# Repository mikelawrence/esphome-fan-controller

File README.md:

# ESPHome RGBCCT LED Controller

<p align="center">

</p>

This is a simple ESP32-C3 based fan controller design to support 4-pin computer fans from 5V to 24V at up to 2 amps. Fan tachometer is supported.

## Web Installation

Goto [Github Pages](https://mikelawrence.github.io/esphome-fan-controller/) if you want to install a prebuilt image and receive automatic update notifications via Home Assistant.

## Status

* **Rev -:** Ordered boards from JLCPCB. Ordered parts from Mouser and Digikey. Board is assembled but there is a problem with the 5V Power Supply. Wait for Rev A.
* **Rev A:** Coming soon!

## Schematic

<p align="center">
     <br />
    Schematic
</p>

## Bill of Materials

<p align="center">
     <br />
    Interactive BOM
</p>

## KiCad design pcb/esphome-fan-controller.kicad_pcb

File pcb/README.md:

# ESPHome RGBCCT LED Controller PCB

<p align="center">

</p>

This is a simple ESP32-C3 based fan controller design to support 4-pin computer fans from 5V to 24V at up to 2 amps. Fan tachometer is supported.

## Status

* **Rev -:** Ordered boards from JLCPCB. Ordered parts from Mouser and Digikey. Currently waiting to put everything together.

## Schematic

<p align="center">
     <br />
    Schematic
</p>

## Bill of Materials

<p align="center">
     <br />
    Interactive BOM
</p>

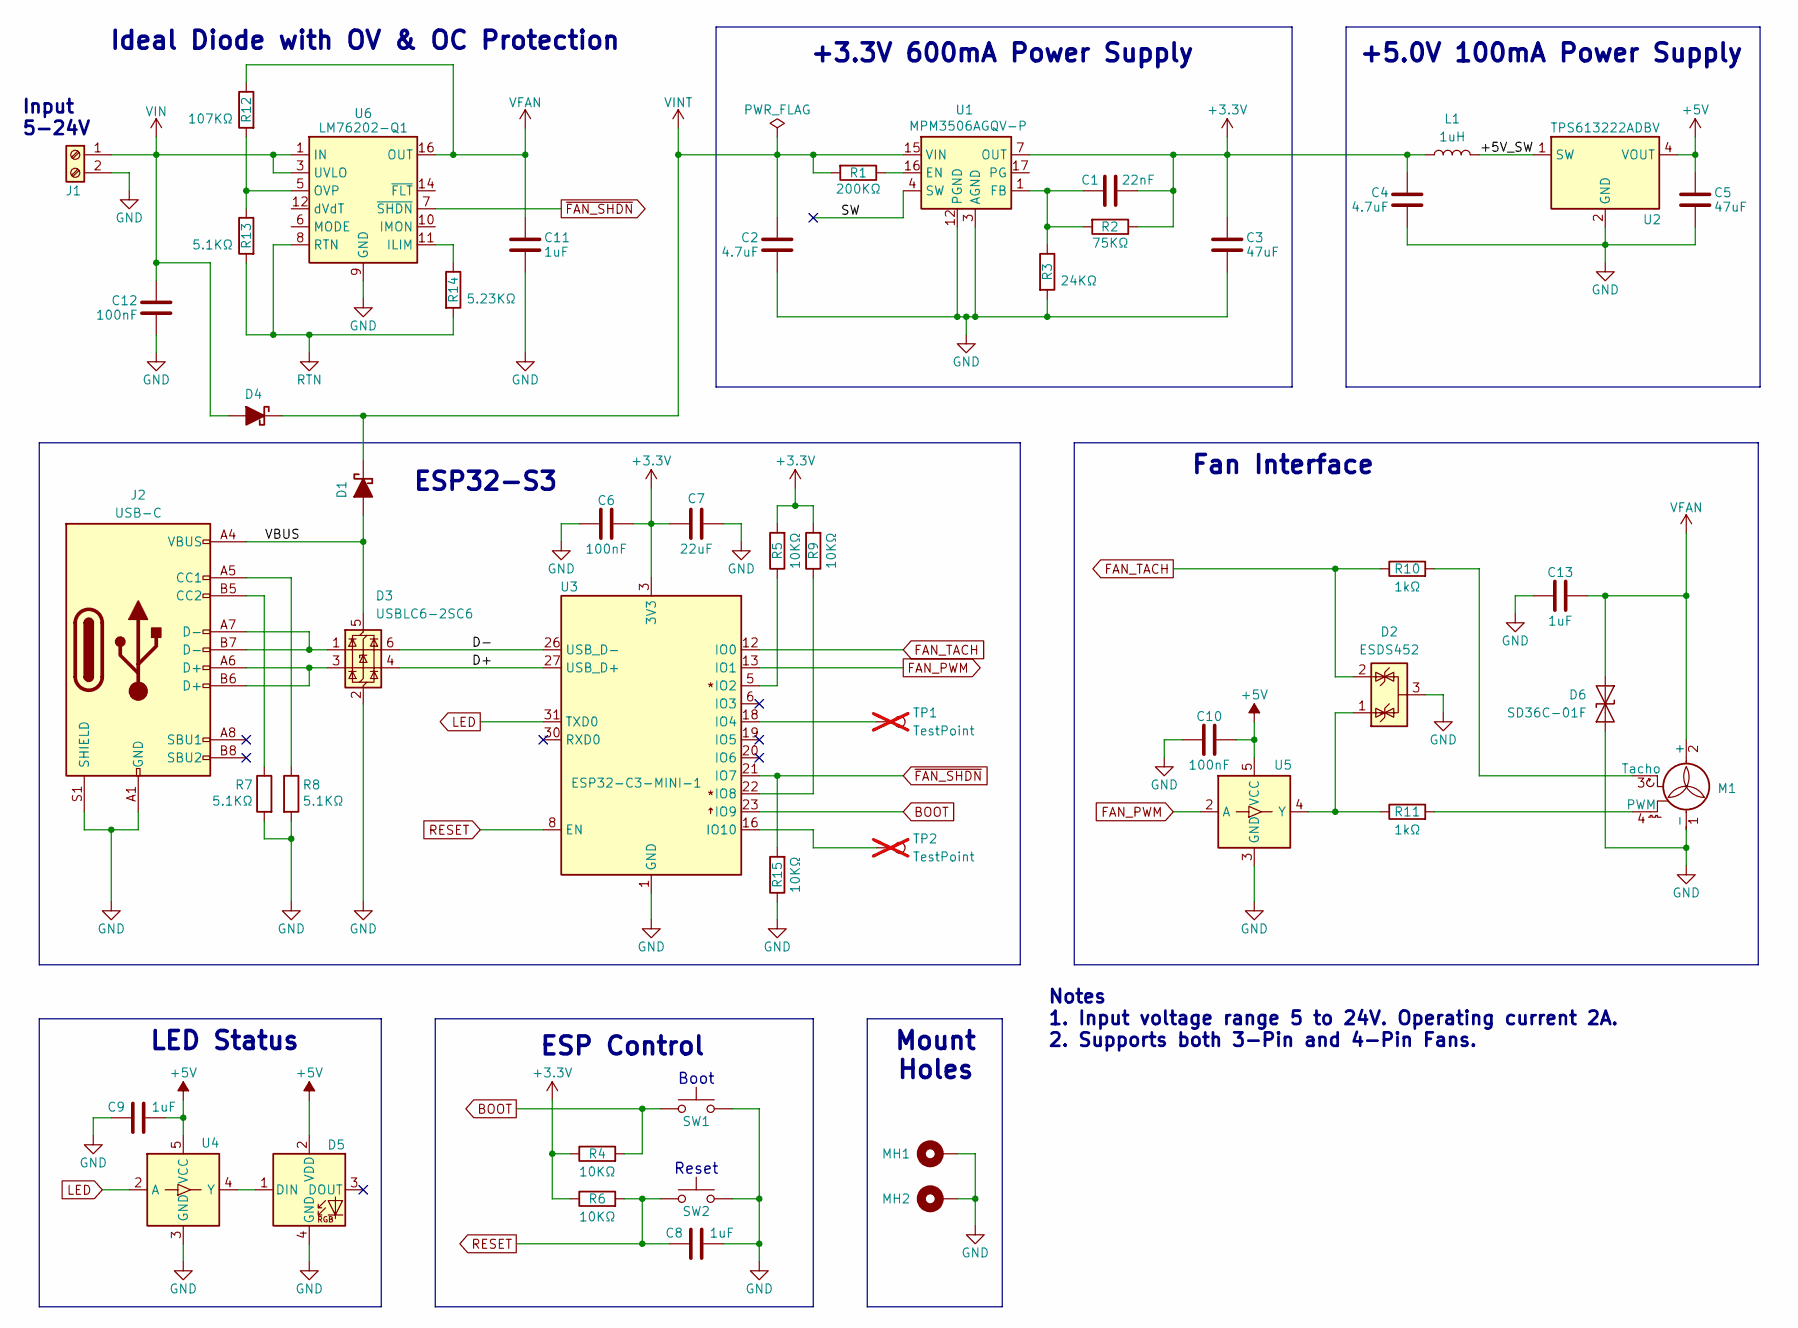
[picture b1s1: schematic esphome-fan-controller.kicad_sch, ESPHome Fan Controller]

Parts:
C1: 22nF; C_0402_1005Metric; Part Number GRM155R71H223KA12J
C2, C4: 4.7uF; C_0805_2012Metric; Part Number MSASU21GBB5475KTNA01
C3, C5: 47uF; C_0805_2012Metric; Part Number MSASL21GBB5476MTNA01
C6, C10, C12: 100nF; C_0402_1005Metric; Part Number CL05B104KB54PNC
C7: 22uF; C_0603_1608Metric; Part Number GRM188R60J226MEA0D
C8, C9: 1uF; C_0402_1005Metric; Part Number CL05A105KA5NQNC
C11, C13: 1uF; C_0805_2012Metric; Part Number CC0805MKY5V9BB105
D1, D4: SS2FH6HM3/H; D_SMF; Part Number SS2FH6HM3/H
D2: ESDS452; SOT-23; Part Number ESDS452DBZR
D3: USBLC6-2SC6; SOT-23-6; Part Number USBLC6-2SC6
D5: SK6812-4020; Part Number 4691
D6: SD36C-01F; D_SOD-323; Part Number SD36C-01FTG
J1: Screw_Terminal_01x02; 1984769; Part Number 1988956
J2: USB-C; HRO_TYPE-C-31-M-12; Part Number 1332645
L1: 1uH; L_0805_2012Metric; Part Number MLP2012S1R0MT0S1
M1: Fan_CPU_4pin; FanPinHeader_1x04_P2.54mm_Vertical; Part Number 47053-1000
MH1, MH2: MountingHole_2.2mm_M2_Pad
R1: 200KΩ; R_0402_1005Metric; Part Number CRCW0402200KFKED
R2: 75KΩ; R_0402_1005Metric; Part Number RT0402BRD0775KL
R3: 24KΩ; R_0402_1005Metric; Part Number RT0402BRD0724KL
R4, R5, R6, R9, R15: 10KΩ; R_0402_1005Metric; Part Number CRCW040210K0FKED
R7, R8, R13: 5.1KΩ; R_0402_1005Metric; Part Number RT0402BRD075K1L
R10, R11: 1kΩ; R_0402_1005Metric; Part Number CRCW04021K0FKED
R12: 107KΩ; R_0402_1005Metric; Part Number RT0402BRD07107KL
R14: 5.23KΩ; R_0402_1005Metric; Part Number RT0402BRD075K23L
SW1, SW2: SW_SPST_B3U-1000P-B; Part Number B3U-1000P
TP1, TP2: TestPoint; TestPoint_THTPad_1.0x1.0mm_Drill0.5mm; not fitted
U1: MPM3506AGQV-P; QFN-19; Part Number MPM3506AGQV-P; Mouser Part Number 946-MPM3506AGQV-P
U2: TPS613222ADBV; SOT-23-5; Part Number TPS613222ADBVR
U3: ESP32-C3-MINI-1; ESP32-C3-MINI-1-N4X; Part Number ESP32-C3-MINI-1-N4X
U4, U5: SN74LV1T34DBV; SOT-23-5; Part Number SN74LV1T34DBV
U6: LM76202-Q1; HTSSOP-16-1EP_4.4x5mm_P0.65mm_EP3.4x5mm_Mask2.66x2.46mm_The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; Part Number LM76202QPWPRQ1

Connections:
+3.3V: C1.2, C3.1, C4.1, C6.2, C7.1, L1.1, R2.1, R4.1, R5.2, R6.1, R9.2, U1.7 (OUT), U1.8 (OUT_2), U1.9 (OUT_3), U1.19 (OUT_4), U3.3 (3V3)
+5V: C5.1, C9.2, C10.2, D5.2 (VDD), U2.4 (VOUT), U4.5 (VCC), U5.5 (VCC)
/+5V_SW: L1.2, U2.1 (SW)
/D+: D3.4 (I/O2), U3.27 (USB_D+)
/D-: D3.6 (I/O1), U3.26 (USB_D-)
/SW: U1.4 (SW), U1.5 (SW_2), U1.6 (SW_3), U1.18 (SW_4)
/VBUS: D1.2 (A), D3.5 (VBUS), J2.A4 (VBUS), J2.B4 (VBUS)
BOOT: R4.2, SW1.2, U3.23 (IO9)
FAN_PWM: U3.13 (IO1), U5.2 (A)
FAN_TACH: D2.2 (K), R10.1, U3.12 (IO0)
GND: C2.2, C3.2, C4.2, C5.2, C6.1, C7.2, C8.2, C9.1, C10.1, C11.2, C12.2, C13.1, D2.3 (A), D3.2 (GND), D5.4 (GND), D6.1 (A1), J1.2, J2.A1 (GND), J2.B1 (GND), J2.S1 (SHIELD), M1.1 (-), MH1.1, MH2.1, R3.2, R7.2, R8.2, R15.1, SW1.1, SW2.1, U1.3 (AGND), U1.12 (PGND), U1.13 (PGND_2), U2.2 (GND), U3.1 (GND), U3.2 (GND), U3.11 (GND), U3.14 (GND), U3.36 (GND), U3.37 (GND), U3.38 (GND), U3.39 (GND), U3.40 (GND), U3.41 (GND), U3.42 (GND), U3.43 (GND), U3.44 (GND), U3.45 (GND), U3.46 (GND), U3.47 (GND), U3.48 (GND), U3.49 (GND), U3.50 (GND), U3.51 (GND), U3.52 (GND), U3.53 (GND), U4.3 (GND), U5.3 (GND), U6.9 (GND)
LED: U3.31 (TXD0), U4.2 (A)
unnamed: D3.1 (I/O1), J2.A7 (D-), J2.B7 (D-)
unnamed: D3.3 (I/O2), J2.A6 (D+), J2.B6 (D+)
unnamed: D5.1 (DIN), U4.4 (Y)
unnamed: J2.A5 (CC1), R8.1
unnamed: J2.B5 (CC2), R7.1
unnamed: M1.4 (PWM), R11.2
unnamed: M1.3 (Tacho), R10.2
unnamed: R1.1, U1.16 (EN)
unnamed: C1.1, R2.2, R3.1, U1.1 (FB)
unnamed: R5.1, U3.5 (IO2)
unnamed: TP1.1, U3.18 (IO4)
unnamed: R9.1, U3.22 (IO8)
unnamed: TP2.1, U3.16 (IO10)
unnamed: D2.1 (K), R11.1, U5.4 (Y)
unnamed: R14.1, U6.11 (ILIM)
unnamed: R12.2, R13.1, U6.5 (OVP)
RESET: C8.1, R6.2, SW2.2, U3.8 (EN)
RTN: R13.2, R14.2, U6.8 (RTN), U6.17 (RTN_1)
VFAN: C11.1, C13.2, D6.2 (A2), M1.2 (+), R12.1, U6.15 (OUT_2), U6.16 (OUT)
VIN: C12.1, D4.2 (A), J1.1, U6.1 (IN), U6.2 (IN_2), U6.3 (UVLO)
VINT: C2.1, D1.1 (K), D4.1 (K), R1.2, U1.15 (VIN)
~FAN_SHDN: R15.2, U3.21 (IO7), U6.7 (~SHDN)

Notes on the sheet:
Mount Holes
Notes 1. Input voltage range 5 to 24V. Operating current 2A. 2. Supports both 3-Pin and 4-Pin Fans.
Ideal Diode with OV & OC Protection
Boot
+5.0V 100mA Power Supply
ESP Control
LED Status
Input 5-24V
+3.3V 600mA Power Supply
ESP32-S3
Fan Interface
Reset

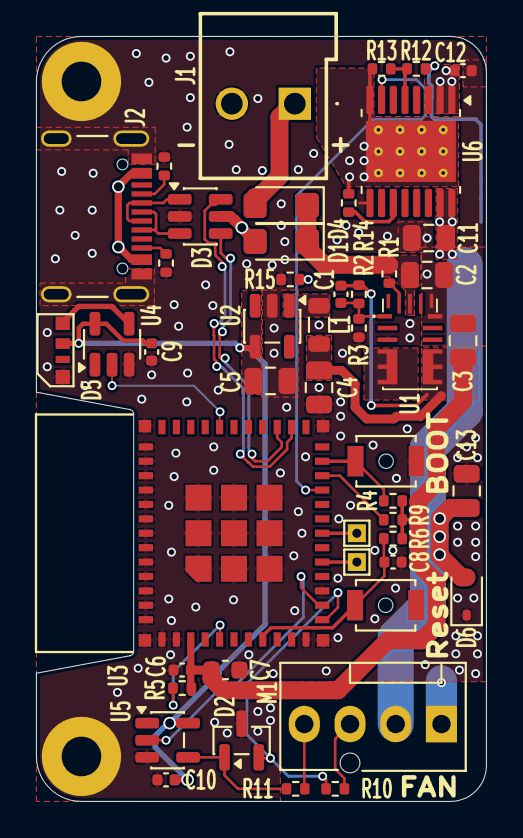
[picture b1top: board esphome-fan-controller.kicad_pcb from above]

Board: 2 copper layers, 25.0 x 42.5 mm, 51 parts (1 on the bottom side), 34 nets.

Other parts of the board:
TEXT1: OSHW-Logo_5.7x6mm_SilkScreen

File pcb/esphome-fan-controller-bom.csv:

"Qty","Reference","Value","Description","Datasheet","Footprint","DNP","Manufacturer","Part Number"
"1","C1","22nF","Capacitor, 22nF, MLCC, 50V, X7R, 10%, 0402","~","Capacitor_SMD:C_0402_1005Metric","","Murata","GRM155R71H223KA12J"
"1","C7","22uF","Capacitor, 22uF, MLCC, 6.3V, X5R, 20%, 0603","~","Capacitor_SMD:C_0603_1608Metric","","Murata","GRM188R60J226MEA0D"
"2","C11,C13","1uF","Capacitor, 1uF, MLCC, 50V, X5R, 20%, 0805","~","Capacitor_SMD:C_0805_2012Metric","","YAGEO","CC0805MKY5V9BB105"
"2","C2,C4","4.7uF","Capacitor, 4.7uF, MLCC, 50V, X5R, 20%, 0805","~","Capacitor_SMD:C_0805_2012Metric","","TAIYO YUDEN","MSASU21GBB5475KTNA01"
"2","C3,C5","47uF","Capacitor, 47uF, MLCC, 10V, X5R, 20%, 0805","~","Capacitor_SMD:C_0805_2012Metric","","TAIYO YUDEN","MSASL21GBB5476MTNA01"
"3","C6,C10,C12","100nF","Capacitor, 100nF, MLCC, 50V, X7R, 10%, 0402","~","Capacitor_SMD:C_0402_1005Metric","","Samsung","CL05B104KB54PNC"
"2","C8,C9","1uF","Capacitor, 1uF, MLCC, 25V, X5R, 10%, 0402","~","Capacitor_SMD:C_0402_1005Metric","","Samsung","CL05A105KA5NQNC"
"1","D2","ESDS452","5.5-V Bi-Directional TVS Diode","https://www.ti.com/lit/ds/symlink/esds452.pdf","Package_TO_SOT_SMD:SOT-23","","Texas Instruments","ESDS452DBZR"
"1","D3","USBLC6-2SC6","Very low capacitance ESD protection diode, 2 data-line, SOT-23-6","https://www.st.com/resource/en/datasheet/usblc6-2.pdf","Package_TO_SOT_SMD:SOT-23-6","","STMicroelectronics","USBLC6-2SC6"
"1","D5","SK6812-4020","RGB LED with integrated controller, 4mm x 2mm Side LED package","https://cdn-shop.adafruit.com/product-files/4691/4691_SK68XX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","SK6812-4020:SK6812-4020","","Adafruit","4691"
"1","D6","SD36C-01F","36V, 450W Discrete Bidirectional TVS Diode, SOD-323","https://www.littelfuse.com/~/media/electronics/datasheets/tv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","Diode_SMD:D_SOD-323","","Littelfuse","SD36C-01FTG"
"2","D1,D4","SS2FH6HM3/H","40V 2A Schottky Barrier Rectifier Diode, SMF(DO-219AB)","https://www.vishay.com/docs/87731/ss2fh6.pdf","Diode_SMD:D_SMF","","Vishay","SS2FH6HM3/H"
"1","J1","Screw_Terminal_01x02","Generic screw terminal, single row, 01x02, script generated (kicad-library-utils/schlib/autogen/connector/)","https://www.phoenixcontact.com/en-us/products/printed-circui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","1984769:1984769","","Phoenix Contact","1988956"
"1","J2","USB-C","Connector, USB 2.0, 16P, Type-C, Receptacle","https://www.usb.org/sites/default/files/documents/usb_type-c.zip","TYPE-C-31-M-12:HRO_TYPE-C-31-M-12","","Phoenix Contact","1332645"
"1","L1","1uH","Inductor, 1uH, 3.3A, 20%, 1008","~","Inductor_SMD:L_0805_2012Metric","","TDK","MLP2012S1R0MT0S1"
"1","M1","Fan_CPU_4pin","CPU Fan, tacho output, PWM input, 4-pin connector","http://www.formfactors.org/developer%5Cspecs%5Crev1_2_public.pdf","Connector:FanPinHeader_1x04_P2.54mm_Vertical","","Molex","47053-1000"
"1","R1","200KΩ","Resistor, 200KΩ, 62.5mW,100PPM, 1%, 0402","~","Resistor_SMD:R_0402_1005Metric","","Vishay / Dale","CRCW0402200KFKED"
"1","R2","75KΩ","Resistor, 75KΩ, 62.5mW, 25PPM, 0.1%, 0402","~","Resistor_SMD:R_0402_1005Metric","","YAGEO","RT0402BRD0775KL"
"1","R3","24KΩ","Resistor, 24KΩ, 62.5mW, 25PPM, 0.1%, 0402","~","Resistor_SMD:R_0402_1005Metric","","YAGEO","RT0402BRD0724KL"
"1","R12","107KΩ","Resistor, 107KΩ, 62.5mW, 25PPM, 0.1%, 0402","~","Resistor_SMD:R_0402_1005Metric","","YAGEO","RT0402BRD07107KL"
"1","R14","5.23KΩ","Resistor, 5.23KΩ, 62.5mW, 25PPM, 0.1%, 0402","~","Resistor_SMD:R_0402_1005Metric","","YAGEO","RT0402BRD075K23L"
"2","R10,R11","1kΩ","Resistor, 1KΩ, 62.5mW,100PPM, 1%, 0402","~","Resistor_SMD:R_0402_1005Metric","","Vishay / Dale","CRCW04021K0FKED"
"5","R4,R5,R6,R9,R15","10KΩ","Resistor, 10KΩ, 62.5mW,100PPM, 1%, 0402","~","Resistor_SMD:R_0402_1005Metric","","Vishay / Dale","CRCW040210K0FKED"
"3","R7,R8,R13","5.1KΩ","Resistor, 5.1KΩ, 62.5mW, 25PPM, 0.1%, 0402","~","Resistor_SMD:R_0402_1005Metric","","YAGEO","RT0402BRD075K1L"
"2","SW1,SW2","~","Switch, SMD","https://omronfs.omron.com/en_US/ecb/products/pdf/en-b3u.pdf","Button_Switch_SMD:SW_SPST_B3U-1000P-B","","Omron","B3U-1000P"
"2","TP1,TP2","TestPoint","Test Point","~","TestPoint:TestPoint_THTPad_1.0x1.0mm_Drill0.5mm","DNP","",""
"1","U1","MPM3506AGQV-P","Switching Voltage Regulators 36V/0.6A Module Sync Step-Down Converter","https://www.monolithicpower.com/pub/media/document/MPM3506A_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","MPM3506A:QFN-19","","Monolithic Power Systems","MPM3506AGQV-P"
"1","U2","TPS613222ADBV","1.8A Step-Up Converter, 5V Output Voltage, 0.9-5.5V Input Voltage, SOT-23-5","http://www.ti.com/lit/ds/symlink/tps61322.pdf","Package_TO_SOT_SMD:SOT-23-5","","Texas Instruments","TPS613222ADBVR"
"1","U3","ESP32-C3-MINI-1","RF Module, ESP32-C3 SoC, Wi-Fi 802.11b/g/n, Bluetooth 5, BLE, 32-bit, 3.3V, onboard antenna, SMD","https://documentation.espressif.com/esp32-c3-mini-1_datashee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","ESP32-C3-MINI:ESP32-C3-MINI-1-N4X","","Espressif Systems","ESP32-C3-MINI-1-N4X"
"1","U6","LM76202-Q1","2.2A Integrated Ideal Diode with Overvoltage and Overcurrent Protection, 4.2 to 60V Input Voltage, HTSSOP-16","https://www.ti.com/lit/ds/symlink/lm76202-q1.pdf","Package_SO:HTSSOP-16-1EP_4.4x5mm_P0.65mm_EP3.4x5mm_Mask2.66x2.46mm_ThermalVias","","Texas Instruments","LM76202QPWPRQ1 "
"2","U4,U5","SN74LV1T34DBV","IC, Single Power Supply, Single Buffer GATE, CMOS Logic, Level Shifter, SOT-23-5","https://www.ti.com/lit/ds/symlink/sn74lv1t34.pdf","Package_TO_SOT_SMD:SOT-23-5","","Texas Instruments","SN74LV1T34DBV"

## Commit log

2026-03-09 Bump actions/upload-artifact from 4.6.2 to 7.0.0
    Bumps [actions/upload-artifact](https://github.com/actions/upload-artifact) from 4.6.2 to 7.0.0.
    - [Release notes](https://github.com/actions/upload-artifact/releases)
    - [Commits](https://github.com/actions/upload-artifact/compare/ea165f8d65b6e75b540449e92b4886f43607fa02...bbbca2ddaa5d8feaa63e36b76fdaad77386f024f)
    ---
    updated-dependencies:
    - dependency-name: actions/upload-artifact
2026-03-09 Bump actions/checkout from 5 to 6
    Bumps [actions/checkout](https://github.com/actions/checkout) from 5 to 6.
    - [Release notes](https://github.com/actions/checkout/releases)
    - [Commits](https://github.com/actions/checkout/compare/v5...v6)
    ---
    updated-dependencies:
    - dependency-name: actions/checkout
2026-03-09 Bump actions/download-artifact from 4.3.0 to 8.0.0
    Bumps [actions/download-artifact](https://github.com/actions/download-artifact) from 4.3.0 to 8.0.0.
    - [Release notes](https://github.com/actions/download-artifact/releases)
    - [Commits](https://github.com/actions/download-artifact/compare/d3f86a106a0bac45b974a628896c90dbdf5c8093...70fc10c6e5e1ce46ad2ea6f2b72d43f7d47b13c3)
    ---
    updated-dependencies:
    - dependency-name: actions/download-artifact
2026-03-09 Fix README links
2026-03-09 Correct path in CI
2026-03-09 Add logger to configuration yaml
2026-03-09 Switch to esphome build and update checkout version
2026-03-09 Remove old version updates in publish pages action
2026-03-09 Working on actions
2026-03-09 Fix config path in build action
2026-03-09 Reorg config files
2026-03-09 Correct config path
2026-03-09 Trying to get Publish Firmware Action working
2026-03-09 Fix incorrect substitution
2026-03-09 One more try to get this working
2026-03-10 Back to ESPHome publish-firmware workflow
2026-03-10 Run Publish Firmware on Pre-Released
2026-03-10 Switch to normal release
2026-03-10 Refactor publish firmware workflow to use workflow_run and add release info retrieval
2026-03-10 Rename workflow to Create Pre-Release and enable prerelease flag
2026-03-10 Enable prerelease flag in create-release workflow
2026-03-10 Revert build firmware action to use esphome/build.yml@v7
2026-03-10 Fix dependency order in upload firmware job to ensure latest release info is used
2026-03-10 Fix dependency reference in upload firmware job to use correct output from get-release-info
2026-03-10 Fix build firmware action to use correct workflow path
2026-03-10 Update build firmware action to use latest workflow version and enable release info outputs
2026-03-10 Update notes on schematic
2026-03-11 Add fan pwm, fan rpm and status led
2026-03-11 Fix READMEs
2026-03-11 Fix name on web page
2026-03-11 Add PCB README back
2026-03-14 Fix dashboard_import pointing to invalid location.
2026-03-14 Add Stencil Jig files
2026-03-14 Default Rainbow effect for Status LED
2026-03-14 Fix YAML error with rainbow light effect
2026-03-14 Remove data sheets
2026-03-14 Create Release action now creates official release instead of pre-release
2026-03-14 Rename Workflow to Create Release and remove version commit
2026-03-17 Preparing to support both 4-Pin and 3-Pin Fans.
2026-03-17 Update Install buttons for 4-Pin and 3-Pin fans
2026-03-17 Update PCB to Rev A 5V power supply now uses TPS613222A. Different package with correct voltage. Replace fan interface ESD diodes with dual TVS in SOT-23 package. Shutdown on LM76202 can be used to r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
